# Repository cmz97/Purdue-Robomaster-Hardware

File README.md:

# Purdue-Robomaster-Hardware
This repository is for purdue university's robomaster club's hardware design. Mostly PCB Design's

Currently, this repository include the following presentable projects:
1.  Fatbot: a robot controller board designed to help ME student learn control theroy
2.  Robomaster controller board: the controller board designed to serve as the central command of the robots in the purdue robomaster clube. More on Purdue Robomaster Club, pls check the website [here](http://Purduerm.com).

# Fatbot #
Fat bot is connected to National Instrument's myRIO board. This robot controller is for Purdue University's ME375 System Controler class. 
## Input from myRIO ##

## 2 cell battery charger ##

## 9 DOF sensor ##

## Motor Drivers ##

## Battery Monitor ##

## 5v 500mA regulator ##

## Outputs ##

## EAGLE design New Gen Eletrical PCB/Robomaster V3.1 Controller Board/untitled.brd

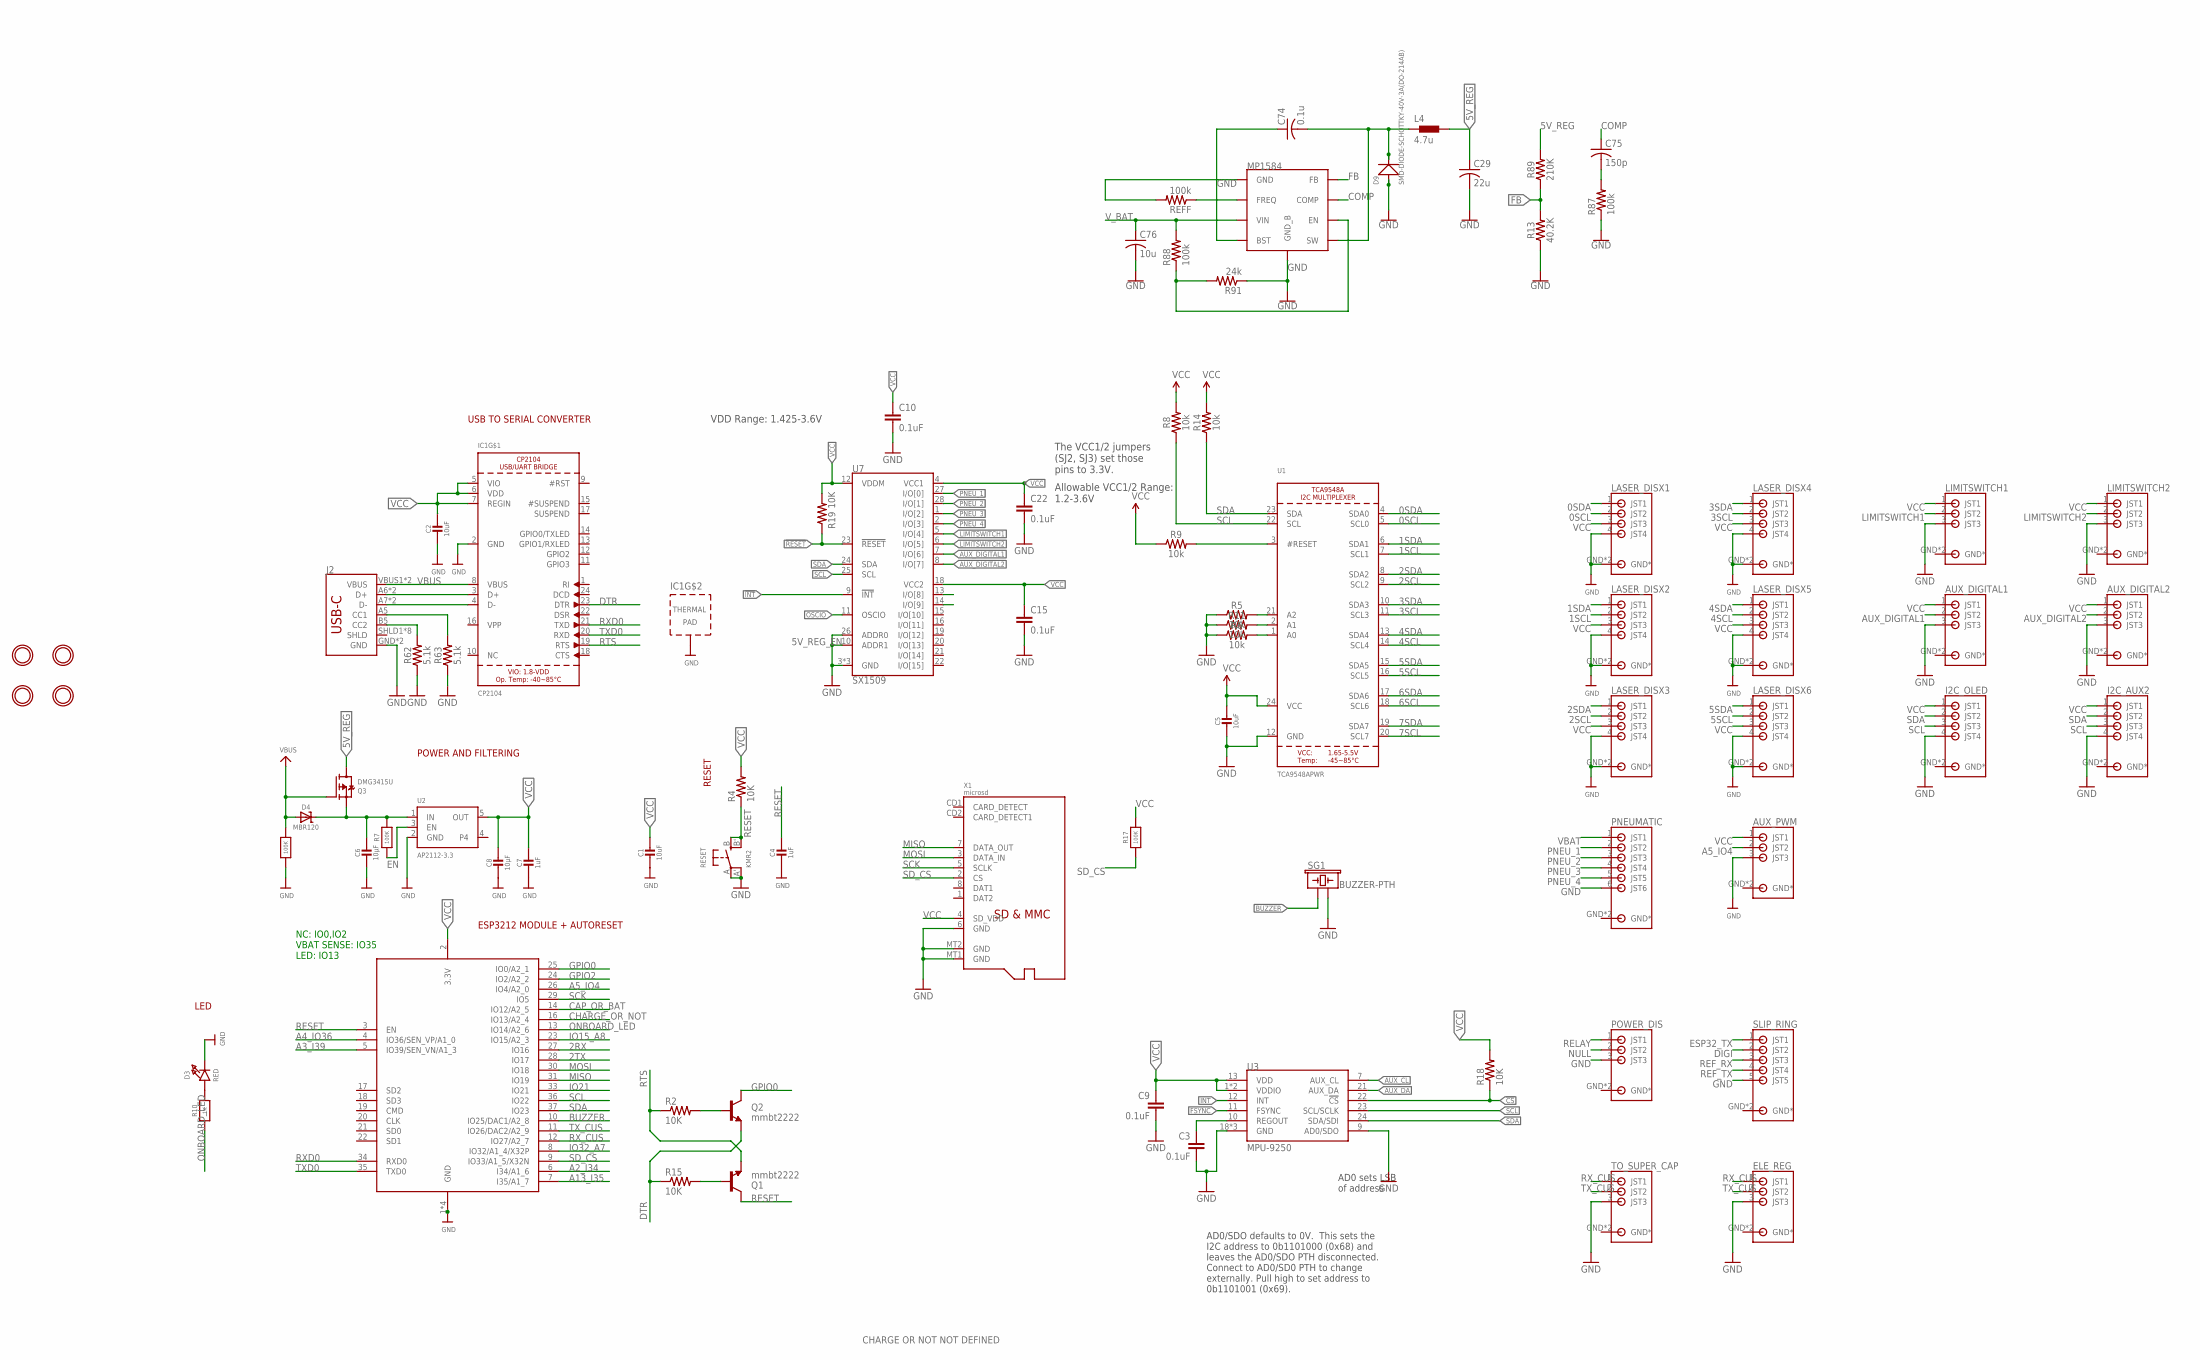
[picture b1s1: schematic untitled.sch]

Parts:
AUX_DIGITAL1, AUX_DIGITAL2: S3B-PH-SM4_TB
AUX_PWM: S3B-PH-SM4_TB
C1, C2, C5: 10uF; 0805-NO
C3, C9, C10, C15, C22: 0.1uF; 0603-CAP
C4, C7: 1uF; 0603-NO
C6, C8: 10µF; 0805-NO
C29: 22u; C1206
C74: 0.1u; C0603
C75: 150p; C0603
C76: 10u; C1206
D3: RED; CHIPLED_0805_NOOUTLINE
D4: MBR120; SOD-123
D9: SMD-DIODE-SCHOTTKY-40V-3A(DO-214AB); DO-214AB
ELE_REG: S3B-PH-SM4_TB
I2C_AUX2, I2C_OLED: S4B-PH-SM4_TB
IC1: CP2104; QFN24_4MM_SMSC
J2: USB_C16PIN; USB-C-16P
L4: 4.7u; MHCI0603-4R7M-R8
LASER_DISX1, LASER_DISX2, LASER_DISX3, LASER_DISX4, LASER_DISX5, LASER_DISX6: S4B-PH-SM4_TB
LIMITSWITCH1, LIMITSWITCH2: S3B-PH-SM4_TB
PNEUMATIC: S6B-PH-SM4_TB
POWER_DIS: S3B-PH-SM4_TB
Q1, Q2: mmbt2222; SOT23-3
Q3: DMG3415U; SOT23-R
R2, R4, R15, R18, R19: 10K; 0603-RES
R5, R6, R8, R9, R11, R14: 10k; 0603
R7, R12, R17: 100K; 0603-NO
R10: 1K; 0603-NO
R13: 40.2K; 0603
R62, R63: 5.1k; 0603
R87, R88: 100k; R0603
R89: 210K; 0603
R91: 24k; R0603
REFF: 100k; R0603
RESET: KMR2; BTN_KMR2_4.6X2.8
SG1: BUZZER-PTH; BUZZER-12MM
SLIP_RING: S5B-PH-SM4_TB
TO_SUPER_CAP: S3B-PH-SM4_TB
U1: TCA9548APWR; TSSOP24
U2: AP2112-3.3; SOT23-5
U3: MPU-9250; QFN24_PAD
U7: SX1509; QFN-28
U$2, U$7, U$10, U$49: MOUNTINGHOLE2.5; MOUNTINGHOLE_2.5_PLATED
U$11: MP1584_V2
X1: microsd; MICROSD
X2: ESP32_WROOM32_SKINNY; WROOM32_SKINNY

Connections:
0SCL: LASER_DISX1.2 (JST2), U1.5 (SCL0)
0SDA: LASER_DISX1.1 (JST1), U1.4 (SDA0)
1SCL: LASER_DISX2.2 (JST2), U1.7 (SCL1)
1SDA: LASER_DISX2.1 (JST1), U1.6 (SDA1)
2RX: X2.27 (IO16)
2SCL: LASER_DISX3.2 (JST2), U1.9 (SCL2)
2SDA: LASER_DISX3.1 (JST1), U1.8 (SDA2)
2TX: X2.28 (IO17)
3SCL: LASER_DISX4.2 (JST2), U1.11 (SCL3)
3SDA: LASER_DISX4.1 (JST1), U1.10 (SDA3)
4SCL: LASER_DISX5.2 (JST2), U1.14 (SCL4)
4SDA: LASER_DISX5.1 (JST1), U1.13 (SDA4)
5SCL: LASER_DISX6.2 (JST2), U1.16 (SCL5)
5SDA: LASER_DISX6.1 (JST1), U1.15 (SDA5)
5V_REG: C29.1, L4.P$2 (2), Q3.3 (D), R89.2
5V_REG_EN1: R88.1, R91.2, U$11.EN
6SCL: U1.18 (SCL6)
6SDA: U1.17 (SDA6)
7SCL: U1.20 (SCL7)
7SDA: U1.19 (SDA7)
!CS: R18.1, U3.22 (!CS)
!INT: U7.9 (!INT)
!RESET: R19.1, U7.23 (!RESET)
A0: R6.2, U1.1 (A0)
A1: R11.2, U1.2 (A1)
A2: R5.2, U1.21 (A2)
A2_I34: X2.6 (I34/A1_6)
A3_I39: X2.5 (IO39/SEN_VN/A1_3)
A4_IO36: X2.4 (IO36/SEN_VP/A1_0)
A5_IO4: AUX_PWM.2 (JST2), X2.26 (IO4/A2_0)
A13_I35: X2.7 (I35/A1_7)
AUX_CL: U3.7 (AUX_CL)
AUX_DA: U3.21 (AUX_DA)
AUX_DIGITAL1: AUX_DIGITAL1.2 (JST2), U7.7 (I/O[6])
AUX_DIGITAL2: AUX_DIGITAL2.2 (JST2), U7.8 (I/O[7])
BST: C74.1, U$11.BST
BUZZER: SG1.+ (1), X2.10 (IO25/DAC1/A2_8)
CAP_OR_BAT: X2.14 (IO12/A2_5)
CC1: J2.A5 (CC1), R63.2
CC2: J2.B5 (CC2), R62.2
CHARGE_OR_NOT: X2.16 (IO13/A2_4)
COMP: C75.1, U$11.COMP
DIGI: SLIP_RING.2 (JST2)
DIR_1: U7.13 (I/O[8])
DIR_2: U7.14 (I/O[9])
DTR: IC1.23 (DTR), Q2.2 (E), R15.1
EN: R7.1, U2.3 (EN)
ESP32_TX: SLIP_RING.1 (JST1)
FB: R13.2, R89.1, U$11.FB
FREQ: REFF.1, U$11.FREQ
FSYNC: U3.11 (FSYNC)
GND: AUX_DIGITAL1.3 (JST3), AUX_DIGITAL2.3 (JST3), AUX_PWM.3 (JST3), C1.2, C2.2, C3.2, C4.2, C5.2, C6.2, C7.2, C8.2, C9.2, C10.2, C15.2, C22.2, C29.2, C76.2, D3.C, D9.1 (+), ELE_REG.3 (JST3), I2C_AUX2.4 (JST4), I2C_OLED.4 (JST4), IC1.2 (GND), IC1.THERM (TP), J2.GND, J2.GND2 (GND), LASER_DISX1.4 (JST4), LASER_DISX1.GND (GND*), LASER_DISX1.GND2 (GND*), LASER_DISX2.4 (JST4), LASER_DISX2.GND (GND*), LASER_DISX2.GND2 (GND*), LASER_DISX3.4 (JST4), LASER_DISX3.GND (GND*), LASER_DISX3.GND2 (GND*), LASER_DISX4.4 (JST4), LASER_DISX4.GND (GND*), LASER_DISX4.GND2 (GND*), LASER_DISX5.4 (JST4), LASER_DISX5.GND (GND*), LASER_DISX5.GND2 (GND*), LASER_DISX6.4 (JST4), LASER_DISX6.GND (GND*), LASER_DISX6.GND2 (GND*), LIMITSWITCH1.3 (JST3), LIMITSWITCH2.3 (JST3), PNEUMATIC.6 (JST6), POWER_DIS.3 (JST3), R5.1, R6.1, R11.1, R12.1, R13.1, R62.1, R63.1, R87.1, R91.1, REFF.2, RESET.A, RESET.A' (P1), SG1.- (2), SLIP_RING.5 (JST5), TO_SUPER_CAP.3 (JST3), U1.12 (GND), U2.2 (GND), U3.9 (AD0/SDO), U3.18 (GND), U3.20 (GND), U3.CENTER (GND), U7.3 (GND), U7.10 (ADDR1), U7.17 (GND), U7.26 (ADDR0), U7.29 (GND), U$11.GND, U$11.GND_B, X1.6 (GND), X1.MT1 (GND), X1.MT2 (GND), X2.1 (GND), X2.15 (GND), X2.38 (GND), X2.P$1 (GND)
GPIO0: Q2.3 (C), X2.25 (IO0/A2_1)
GPIO2: X2.24 (IO2/A2_2)
INT: U3.12 (INT)
IO15_A8: X2.23 (IO15/A2_3)
IO21: X2.33 (IO21)
IO32_A7: X2.8 (IO32/A1_4/X32P)
LIMITSWITCH1: LIMITSWITCH1.2 (JST2), U7.5 (I/O[4])
LIMITSWITCH2: LIMITSWITCH2.2 (JST2), U7.6 (I/O[5])
MISO: X1.7 (DATA_OUT), X2.31 (IO19)
MOSI: X1.3 (DATA_IN), X2.30 (IO18)
unnamed: C75.2, R87.2
unnamed: D3.A, R10.2
unnamed: C6.1, D4.C, Q3.2 (S), R7.2, U2.1 (IN)
unnamed: R9.2, U1.3 (#RESET)
unnamed: Q1.1 (B), R15.2
unnamed: Q2.1 (B), R2.2
unnamed: IC1.3 (D+), J2.A6 (D+), J2.B6 (D+)
unnamed: IC1.4 (D-), J2.A7 (D-), J2.B7 (D-)
NULL: POWER_DIS.2 (JST2)
ONBOARD_LED: R10.1, X2.13 (IO14/A2_6)
OSCIO: U7.11 (OSCIO)
PNEU_1: PNEUMATIC.2 (JST2), U7.27 (I/O[0])
PNEU_2: PNEUMATIC.3 (JST3), U7.28 (I/O[1])
PNEU_3: PNEUMATIC.4 (JST4), U7.1 (I/O[2])
PNEU_4: PNEUMATIC.5 (JST5), U7.2 (I/O[3])
REF_RX: SLIP_RING.3 (JST3)
REF_TX: SLIP_RING.4 (JST4)
REGOUT: C3.1, U3.10 (REGOUT)
RELAY: POWER_DIS.1 (JST1)
RESET: C4.1, Q1.3 (C), R4.1, RESET.B (S), RESET.B' (S1), X2.3 (EN)
RTS: IC1.19 (RTS), Q1.2 (E), R2.1
RXD0: IC1.21 (TXD), X2.34 (RXD0)
RX_CUS: ELE_REG.1 (JST1), TO_SUPER_CAP.1 (JST1), X2.12 (IO27/A2_7)
SCK: X1.5 (SCLK), X2.29 (IO5)
SCL: I2C_AUX2.3 (JST3), I2C_OLED.3 (JST3), R8.1, U1.22 (SCL), U3.23 (SCL/SCLK), U7.25 (SCL), X2.36 (IO22)
SDA: I2C_AUX2.2 (JST2), I2C_OLED.2 (JST2), R14.1, U1.23 (SDA), U3.24 (SDA/SDI), U7.24 (SDA), X2.37 (IO23)
SD_CS: R17.1, X1.2 (CS), X2.9 (IO33/A1_5/X32N)
SW: C74.2, D9.2 (-), L4.P$1 (1), U$11.SW
TXD0: IC1.20 (RXD), X2.35 (TXD0)
TX_CUS: ELE_REG.2 (JST2), TO_SUPER_CAP.2 (JST2), X2.11 (IO26/DAC2/A2_9)
VBAT: PNEUMATIC.1 (JST1)
VBUS: D4.A, IC1.8 (VBUS), J2.VBUS1 (VBUS), J2.VBUS2 (VBUS), Q3.1 (G), R12.2
VCC: AUX_DIGITAL1.1 (JST1), AUX_DIGITAL2.1 (JST1), AUX_PWM.1 (JST1), C1.1, C2.1, C5.1, C7.1, C8.1, C9.1, C10.1, C15.1, C22.1, I2C_AUX2.1 (JST1), I2C_OLED.1 (JST1), IC1.5 (VIO), IC1.6 (VDD), IC1.7 (REGIN), LASER_DISX1.3 (JST3), LASER_DISX2.3 (JST3), LASER_DISX3.3 (JST3), LASER_DISX4.3 (JST3), LASER_DISX5.3 (JST3), LASER_DISX6.3 (JST3), LIMITSWITCH1.1 (JST1), LIMITSWITCH2.1 (JST1), R4.2, R8.2, R9.1, R14.2, R17.2, R18.2, R19.2, U1.24 (VCC), U2.5 (OUT), U3.1 (VDDIO), U3.8 (VDDIO), U3.13 (VDD), U7.4 (VCC1), U7.12 (VDDM), U7.18 (VCC2), X1.4 (SD_VDD), X2.2 (3.3V)
V_BAT: C76.1, R88.2, U$11.VIN

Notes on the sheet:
POWER AND FILTERING
RESET
USB TO SERIAL CONVERTER
LED
ESP3212 MODULE + AUTORESET
NC: IO0,IO2 VBAT SENSE: IO35 LED: IO13
CHARGE OR NOT NOT DEFINED
AD0/SDO defaults to 0V. This sets the I2C address to 0b1101000 (0x68) and leaves the AD0/SDO PTH disconnected. Connect to AD0/SD0 PTH to change externally. Pull high to set address to 0b1101001 (0x69).
AD0 sets LSB of address
The VCC1/2 jumpers (SJ2, SJ3) set those pins to 3.3V.
VDD Range: 1.425-3.6V
Allowable VCC1/2 Range: 1.2-3.6V

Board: 4 copper layers, 79 parts (21 on the bottom side), 65 nets, no tracks yet.

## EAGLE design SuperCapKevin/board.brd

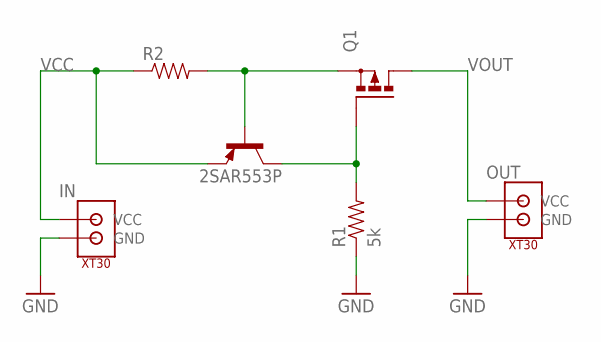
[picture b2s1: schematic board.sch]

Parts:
2SAR553P: -PNP-SOT89-ECB; SOT89-ECB
IN: XT30
OUT: XT30
Q1: P-MOSFET-SO8; SO-08
R1: 5k; 1206
R2: RESISTOR2512; R2512

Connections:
GND: IN.P$1 (GND), OUT.P$1 (GND), R1.1
unnamed: 2SAR553P.C, Q1.4 (G), R1.2
unnamed: 2SAR553P.B, Q1.1 (S), Q1.2 (S), Q1.3 (S), R2.2
VCC: 2SAR553P.E, IN.P$2 (VCC), R2.1
VOUT: OUT.P$2 (VCC), Q1.5 (D), Q1.6 (D), Q1.7 (D), Q1.8 (D)

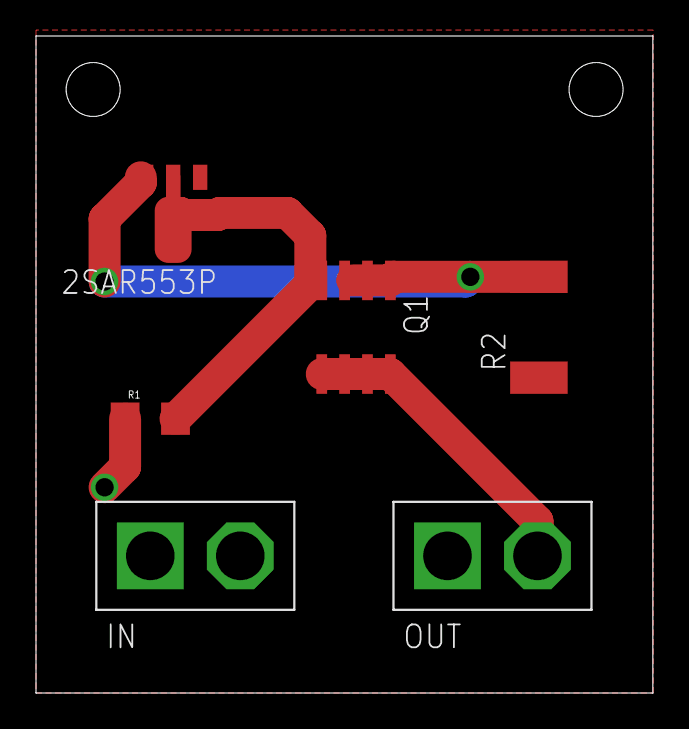
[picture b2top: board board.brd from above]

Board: 2 copper layers, 34.3 x 36.5 mm, 6 parts (0 on the bottom side), 5 nets.

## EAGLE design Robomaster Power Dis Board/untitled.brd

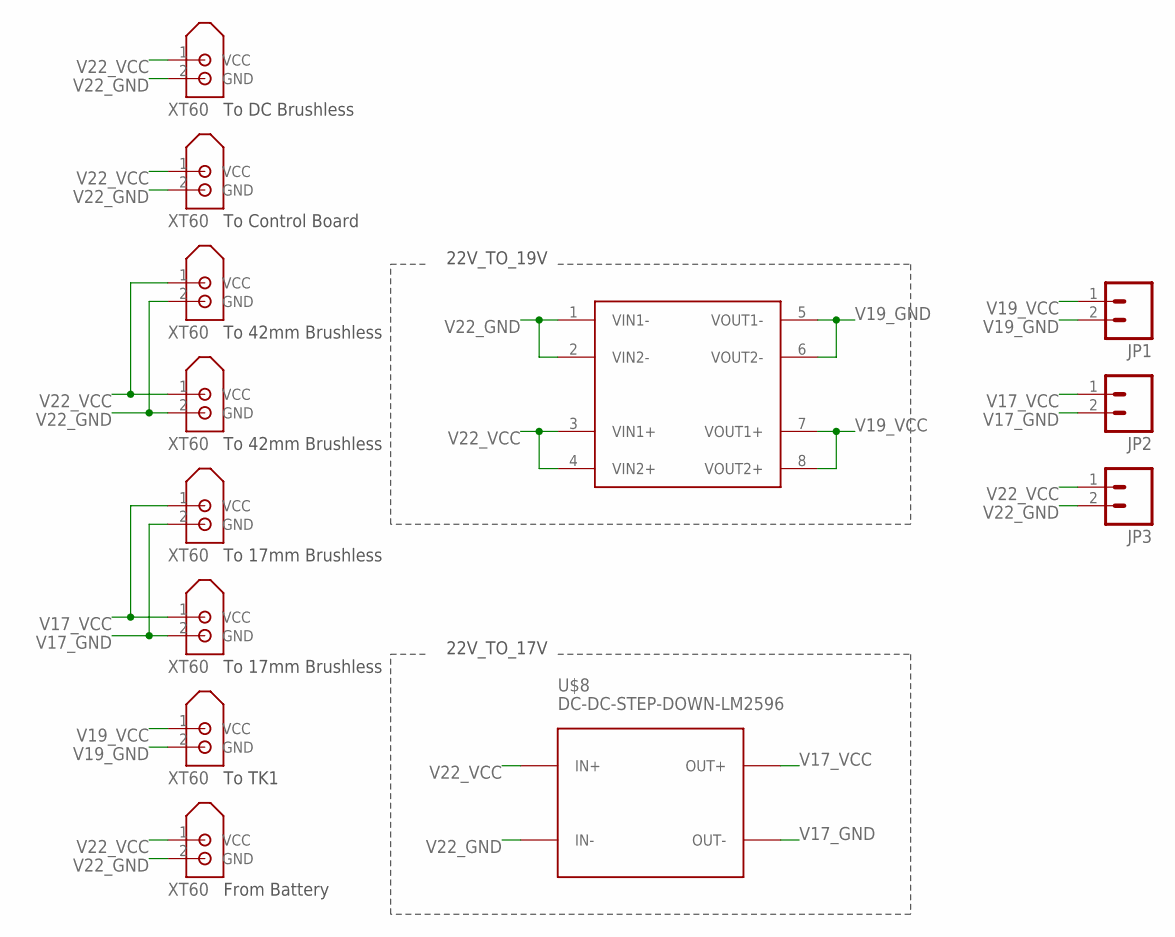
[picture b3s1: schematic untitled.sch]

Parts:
JP1, JP2, JP3: M02JST-PTH-VERT; JST-2-PTH-VERT
U$1, U$2, U$3, U$4, U$5, U$6, U$9, U$10: XT60
U$7: MP1584; MP1584_AMAZON
U$8: DC-DC-STEP-DOWN-LM2596

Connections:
V17_GND: JP2.2, U$3.2 (GND), U$4.2 (GND), U$8.OUT-
V17_VCC: JP2.1, U$3.1 (VCC), U$4.1 (VCC), U$8.OUT+
V19_GND: JP1.2, U$2.2 (GND), U$7.5 (VOUT1-), U$7.6 (VOUT2-)
V19_VCC: JP1.1, U$2.1 (VCC), U$7.7 (VOUT1+), U$7.8 (VOUT2+)
V22_GND: JP3.2, U$1.2 (GND), U$5.2 (GND), U$6.2 (GND), U$7.1 (VIN1-), U$7.2 (VIN2-), U$8.IN-, U$9.2 (GND), U$10.2 (GND)
V22_VCC: JP3.1, U$1.1 (VCC), U$5.1 (VCC), U$6.1 (VCC), U$7.3 (VIN1+), U$7.4 (VIN2+), U$8.IN+, U$9.1 (VCC), U$10.1 (VCC)

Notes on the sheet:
22V_TO_19V
22V_TO_17V
From Battery
To TK1
To 17mm Brushless
To 42mm Brushless
To 42mm Brushless
To Control Board
To DC Brushless

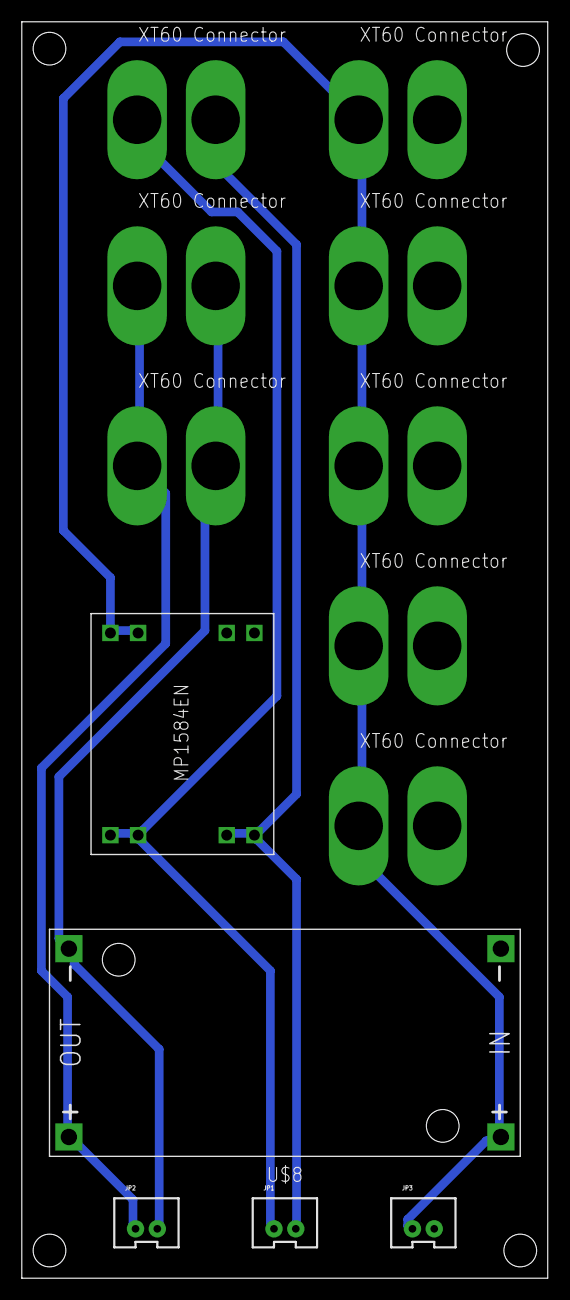
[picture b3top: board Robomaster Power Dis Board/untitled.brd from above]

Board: 2 copper layers, 48.2 x 115.2 mm, 13 parts (0 on the bottom side), 6 nets.

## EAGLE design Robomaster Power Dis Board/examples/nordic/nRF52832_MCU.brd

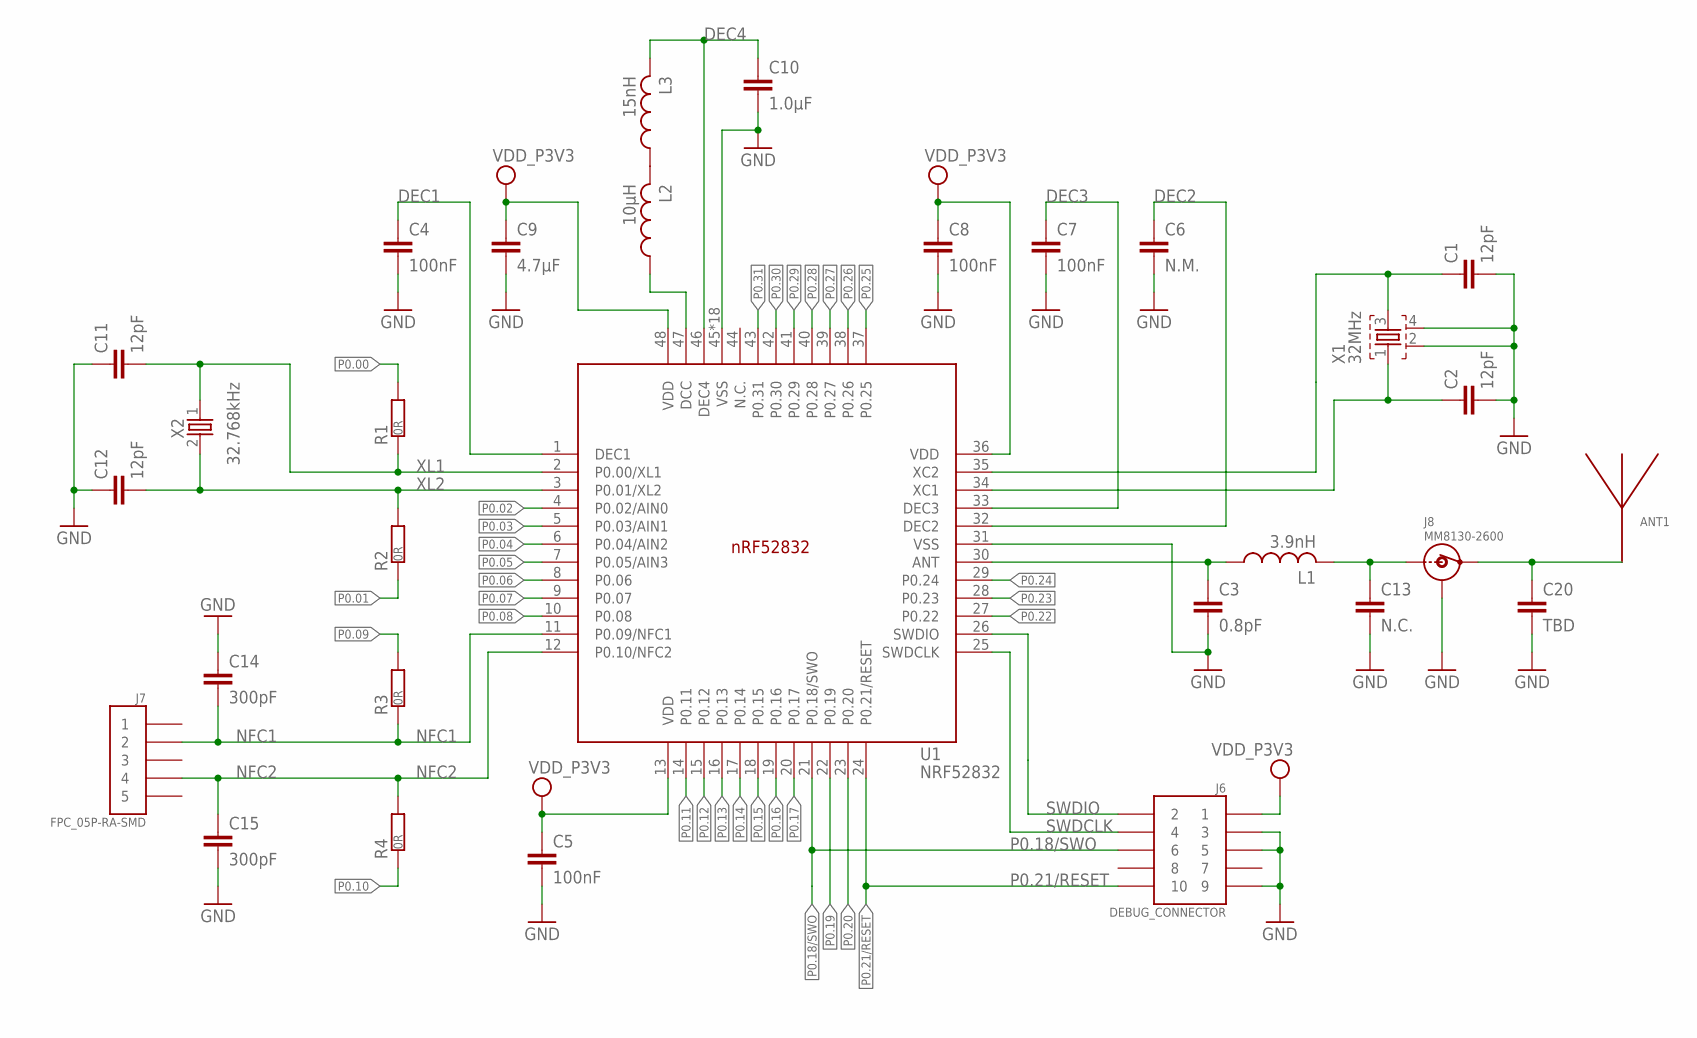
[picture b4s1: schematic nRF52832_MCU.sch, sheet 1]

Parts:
ANT1: ANTENNA_QUARTER-WAVE_MONOPOLE_MEANDERED_LEFT; QWMP_MEANDERED_LEFT_+6
C1, C2, C11, C12: 12pF; RESC0402_N
C3: 0.8pF; RESC0402_N
C4, C5, C7, C8: 100nF; RESC0402_N
C6: N.M.; RESC0402_N
C9: 4.7µF; RESC0603_N
C10: 1.0µF; RESC0603_N
C13: N.C.; RESC0402_N
C14, C15: 300pF; RESC0402_N
C20: TBD; RESC0402_N
J6: DEBUG_CONNECTOR; HDRV127P5X2-10_N
J7: FPC_05P-RA-SMD
J8: MM8130-2600
L1: 3.9nH; RESC0402_N
L2: 10µH; RESC0603_N
L3: 15nH; RESC0402_N
R1, R2, R3, R4: 0R; RESC0402_N
U1: NRF52832; QFN40P600X600X90-48_N
X1: 32MHz; BT-XTAL_2016_N
X2: 32.768kHz; XTAL_3215_N

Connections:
ANT: C3.1, L1.1, U1.30 (ANT)
DEC1: C4.1, U1.1 (DEC1)
DEC2: C6.1, U1.32 (DEC2)
DEC3: C7.1, U1.33 (DEC3)
DEC4: C10.1, L3.2, U1.46 (DEC4)
GND: C1.2, C2.2, C3.2, C4.2, C5.2, C6.2, C7.2, C8.2, C9.2, C10.2, C11.1, C12.1, C13.2, C14.1, C15.2, C20.2, J6.3, J6.5, J6.9, J8.1, J8.2, J8.3, J8.4, U1.31 (VSS), U1.45 (VSS), U1.PAD (VSS), U1.PAD@VIA01 (VSS), U1.PAD@VIA02 (VSS), U1.PAD@VIA03 (VSS), U1.PAD@VIA04 (VSS), U1.PAD@VIA05 (VSS), U1.PAD@VIA06 (VSS), U1.PAD@VIA07 (VSS), U1.PAD@VIA08 (VSS), U1.PAD@VIA09 (VSS), U1.PAD@VIA10 (VSS), U1.PAD@VIA11 (VSS), U1.PAD@VIA12 (VSS), U1.PAD@VIA13 (VSS), U1.PAD@VIA14 (VSS), U1.PAD@VIA15 (VSS), U1.PAD@VIA16 (VSS), X1.2, X1.4; also elsewhere on the board
unnamed: ANT1.P$1, C20.1, J8.OUT
unnamed: L2.2, L3.1
unnamed: C1.1, U1.35 (XC2), X1.3
unnamed: L2.1, U1.47 (DCC)
unnamed: C13.1, J8.IN, L1.2
NFC1: C14.2, J7.2, R3.1, U1.11 (P0.09/NFC1)
NFC2: C15.1, J7.4, R4.2, U1.12 (P0.10/NFC2)
P0.00: R1.2; also elsewhere on the board
P0.01: R2.1; also elsewhere on the board
P0.02: U1.4 (P0.02/AIN0); also elsewhere on the board
P0.03: U1.5 (P0.03/AIN1); also elsewhere on the board
P0.04: U1.6 (P0.04/AIN2); also elsewhere on the board
P0.05: U1.7 (P0.05/AIN3); also elsewhere on the board
P0.06: U1.8 (P0.06); also elsewhere on the board
P0.07: U1.9 (P0.07); also elsewhere on the board
P0.08: U1.10 (P0.08); also elsewhere on the board
P0.09: R3.2; also elsewhere on the board
P0.10: R4.1; also elsewhere on the board
P0.11: U1.14 (P0.11); also elsewhere on the board
P0.12: U1.15 (P0.12); also elsewhere on the board
P0.13: U1.16 (P0.13); also elsewhere on the board
P0.14: U1.17 (P0.14); also elsewhere on the board
P0.15: U1.18 (P0.15); also elsewhere on the board
P0.16: U1.19 (P0.16); also elsewhere on the board
P0.17: U1.20 (P0.17); also elsewhere on the board
P0.18/SWO: J6.6, U1.21 (P0.18/SWO); also elsewhere on the board
P0.19: U1.22 (P0.19); also elsewhere on the board
P0.20: U1.23 (P0.20); also elsewhere on the board
P0.21/RESET: J6.10, U1.24 (P0.21/RESET); also elsewhere on the board
P0.22: U1.27 (P0.22); also elsewhere on the board
P0.23: U1.28 (P0.23); also elsewhere on the board
P0.24: U1.29 (P0.24); also elsewhere on the board
P0.25: U1.37 (P0.25); also elsewhere on the board
P0.26: U1.38 (P0.26); also elsewhere on the board
P0.27: U1.39 (P0.27); also elsewhere on the board
P0.28: U1.40 (P0.28); also elsewhere on the board
P0.29: U1.41 (P0.29); also elsewhere on the board
P0.30: U1.42 (P0.30); also elsewhere on the board
P0.31: U1.43 (P0.31); also elsewhere on the board
SWDCLK: J6.4, U1.25 (SWDCLK)
SWDIO: J6.2, U1.26 (SWDIO)
VDD_P3V3: C5.1, C8.1, C9.1, J6.1, U1.13 (VDD), U1.36 (VDD), U1.48 (VDD); also elsewhere on the board
X1: C2.1, U1.34 (XC1), X1.1
XL1: C11.2, R1.1, U1.2 (P0.00/XL1), X2.1
XL2: C12.2, R2.2, U1.3 (P0.01/XL2), X2.2

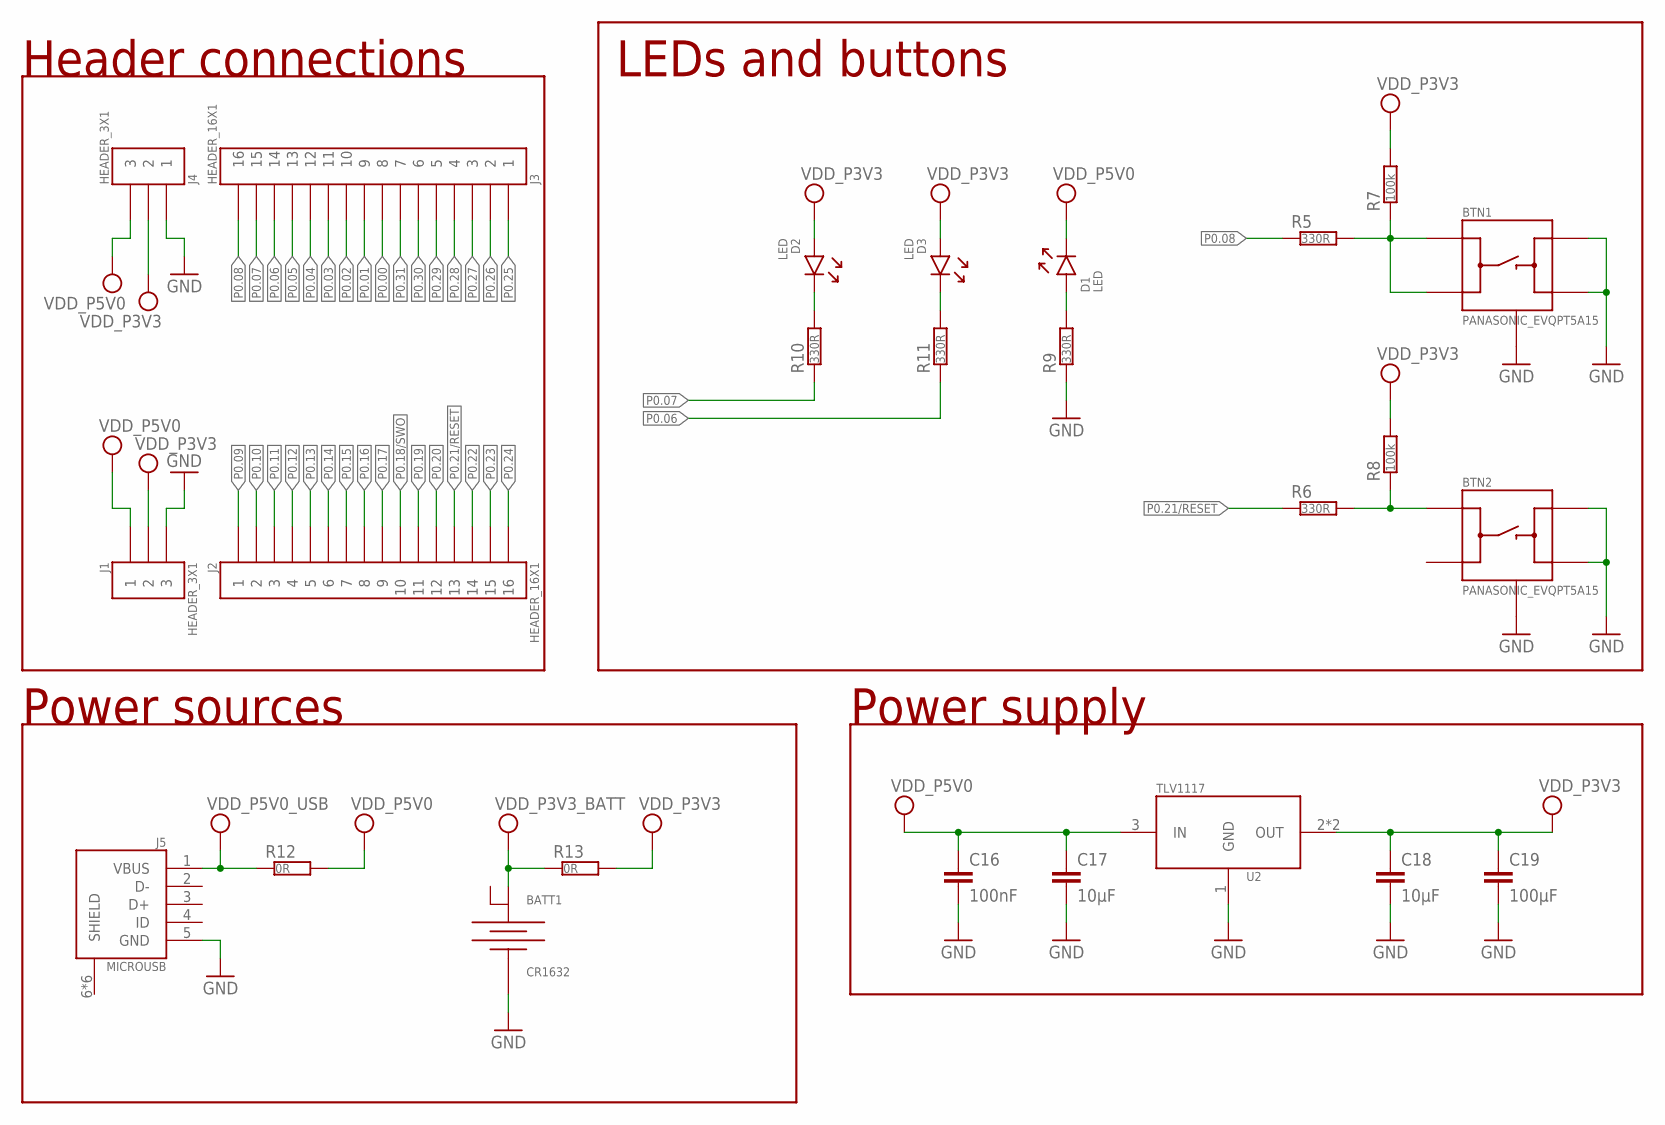
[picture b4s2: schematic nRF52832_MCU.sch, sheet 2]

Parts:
BATT1: CR1632; CR1632_HOLDER_TH
BTN1, BTN2: PANASONIC_EVQPT5A15
C16: 100nF; RESC0402_N
C17, C18: 10µF; RESC0603_N
C19: 100µF; RESC0805_N
D1, D2, D3: LED; DIOC0603_N
J1, J4: HEADER_3X1; HDRV3W64P254_1X3_762X254X900B_NO_SILK
J2, J3: HEADER_16X1; HDRV16W64P254_1X16_4064X254X900B_NO_SILK
J5: MICROUSB; USB-MICRO-B-RA-SMD-PIP
R5, R6, R9, R10, R11: 330R; RESC0402_N
R7, R8: 100k; RESC0402_N
R12, R13: 0R; RESC0402_N
U2: TLV1117; SOT220P700-4_N

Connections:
GND: BATT1.1 (-), BTN1.3 (B), BTN1.4 (B'), BTN1.5 (GND), BTN1.6 (GND), BTN2.3 (B), BTN2.4 (B'), BTN2.5 (GND), BTN2.6 (GND), C16.2, C17.2, C18.2, C19.2, J1.P$3 (3), J4.P$1 (1), J5.5 (GND), R9.1, U2.1 (GND); also elsewhere on the board
unnamed: BTN2.1 (A), R6.2, R8.1
unnamed: BTN1.1 (A), BTN1.2 (A'), R5.2, R7.1
unnamed: D2.1 (C), R10.2
unnamed: D3.1 (C), R11.2
P0.00: J3.P$8 (8); also elsewhere on the board
P0.01: J3.P$9 (9); also elsewhere on the board
P0.02: J3.P$10 (10); also elsewhere on the board
P0.03: J3.P$11 (11); also elsewhere on the board
P0.04: J3.P$12 (12); also elsewhere on the board
P0.05: J3.P$13 (13); also elsewhere on the board
P0.06: J3.P$14 (14), R11.1; also elsewhere on the board
P0.07: J3.P$15 (15), R10.1; also elsewhere on the board
P0.08: J3.P$16 (16), R5.1; also elsewhere on the board
P0.09: J2.P$1 (1); also elsewhere on the board
P0.10: J2.P$2 (2); also elsewhere on the board
P0.11: J2.P$3 (3); also elsewhere on the board
P0.12: J2.P$4 (4); also elsewhere on the board
P0.13: J2.P$5 (5); also elsewhere on the board
P0.14: J2.P$6 (6); also elsewhere on the board
P0.15: J2.P$7 (7); also elsewhere on the board
P0.16: J2.P$8 (8); also elsewhere on the board
P0.17: J2.P$9 (9); also elsewhere on the board
P0.18/SWO: J2.P$10 (10); also elsewhere on the board
P0.19: J2.P$11 (11); also elsewhere on the board
P0.20: J2.P$12 (12); also elsewhere on the board
P0.21/RESET: J2.P$13 (13), R6.1; also elsewhere on the board
P0.22: J2.P$14 (14); also elsewhere on the board
P0.23: J2.P$15 (15); also elsewhere on the board
P0.24: J2.P$16 (16); also elsewhere on the board
P0.25: J3.P$1 (1); also elsewhere on the board
P0.26: J3.P$2 (2); also elsewhere on the board
P0.27: J3.P$3 (3); also elsewhere on the board
P0.28: J3.P$4 (4); also elsewhere on the board
P0.29: J3.P$5 (5); also elsewhere on the board
P0.30: J3.P$6 (6); also elsewhere on the board
P0.31: J3.P$7 (7); also elsewhere on the board
VCC_P5V0_USB: J5.1 (VBUS), R12.1
VDD_LED: D1.2 (A), R9.2
VDD_P3V3: C18.1, C19.1, D2.2 (A), D3.2 (A), J1.P$2 (2), J4.P$2 (2), R7.2, R8.2, R13.2, U2.2 (OUT), U2.4 (OUT); also elsewhere on the board
VDD_P3V3_BATT: BATT1.2 (+), R13.1
VDD_P5V0: C16.1, C17.1, D1.1 (C), J1.P$1 (1), J4.P$3 (3), R12.2, U2.3 (IN)

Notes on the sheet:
Power supply
Power sources
Header connections
LEDs and buttons

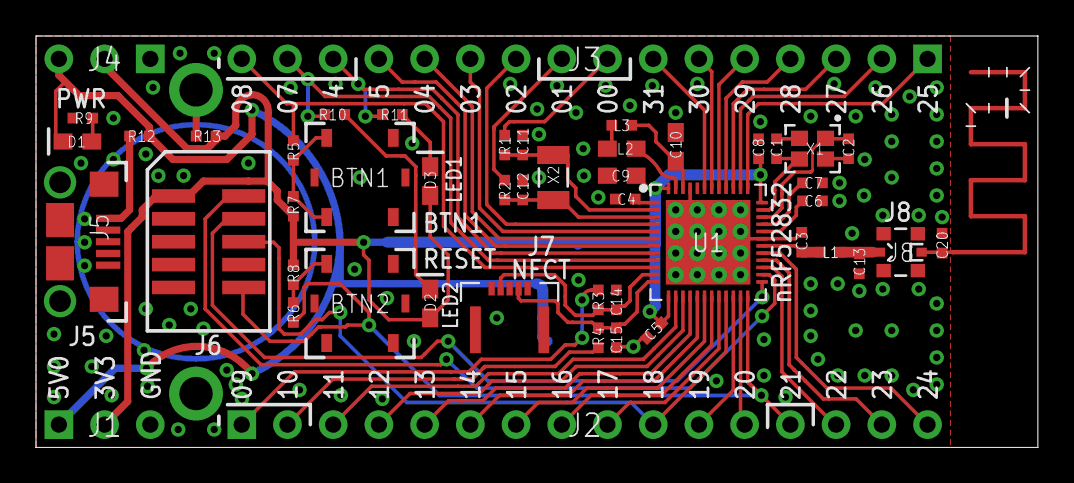
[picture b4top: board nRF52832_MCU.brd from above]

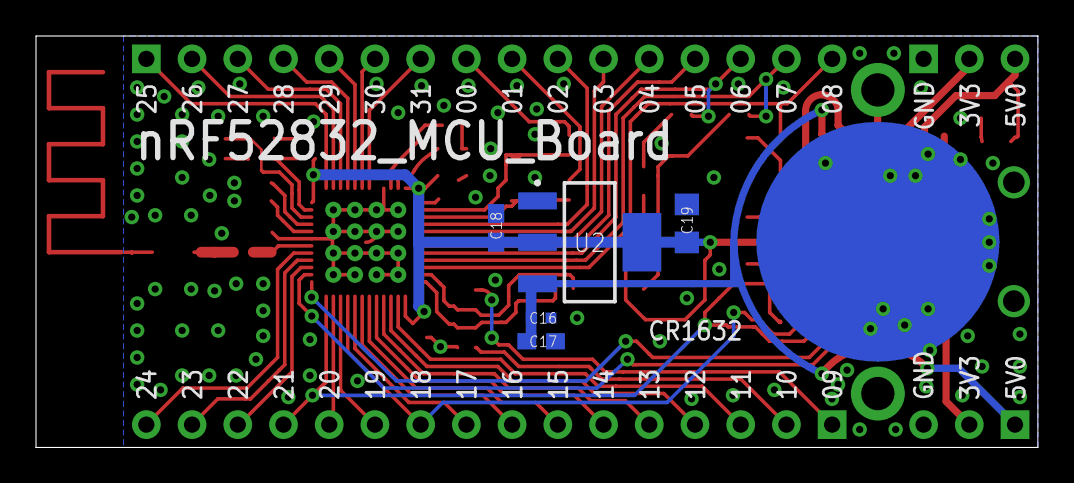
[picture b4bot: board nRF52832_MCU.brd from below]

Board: 2 copper layers, 55.7 x 22.9 mm, 55 parts (6 on the bottom side), 59 nets.

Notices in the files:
parts and their libraries:
microbuilder: This work is placed in the public domain, and may be freely used for commercial and non-commercial work with the following conditions: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
SparkFun: Licensing: CC v3.0 Share-Alike You are welcome to use this library for commercial purposes.
